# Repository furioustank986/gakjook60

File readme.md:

KiCad libraries get messed up when pulling, so just make sure to manage that

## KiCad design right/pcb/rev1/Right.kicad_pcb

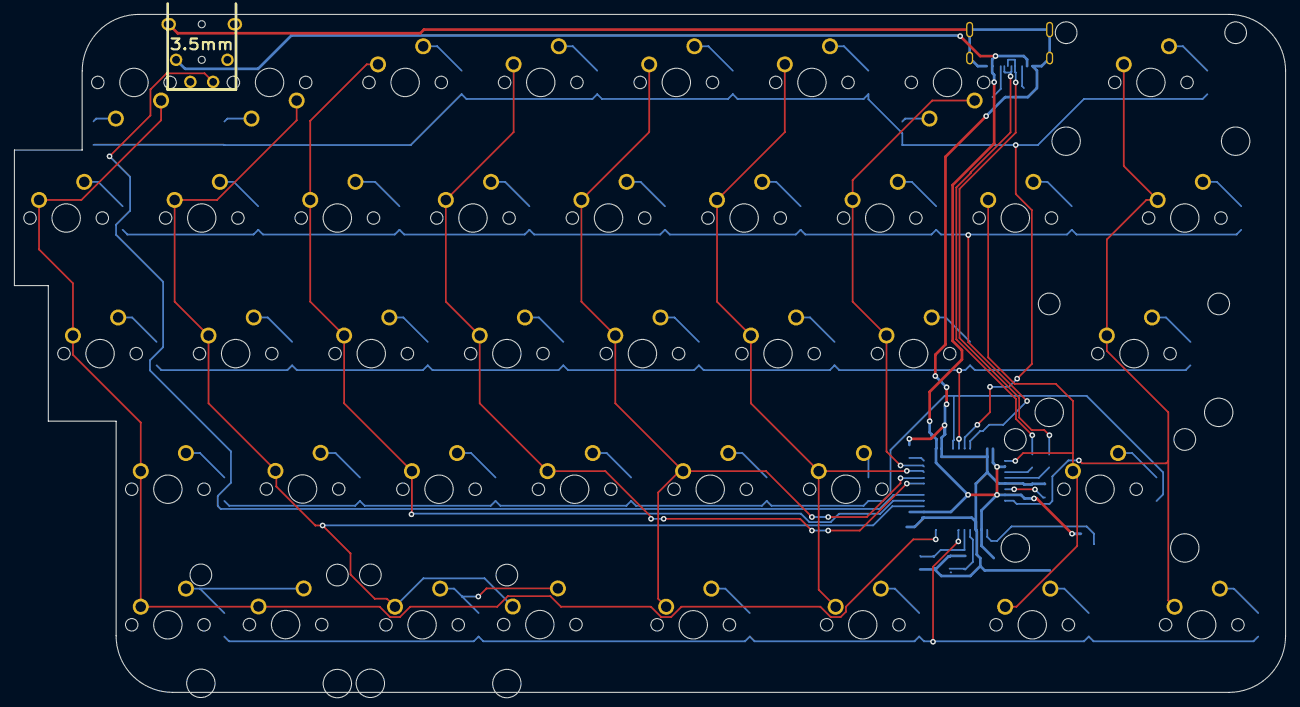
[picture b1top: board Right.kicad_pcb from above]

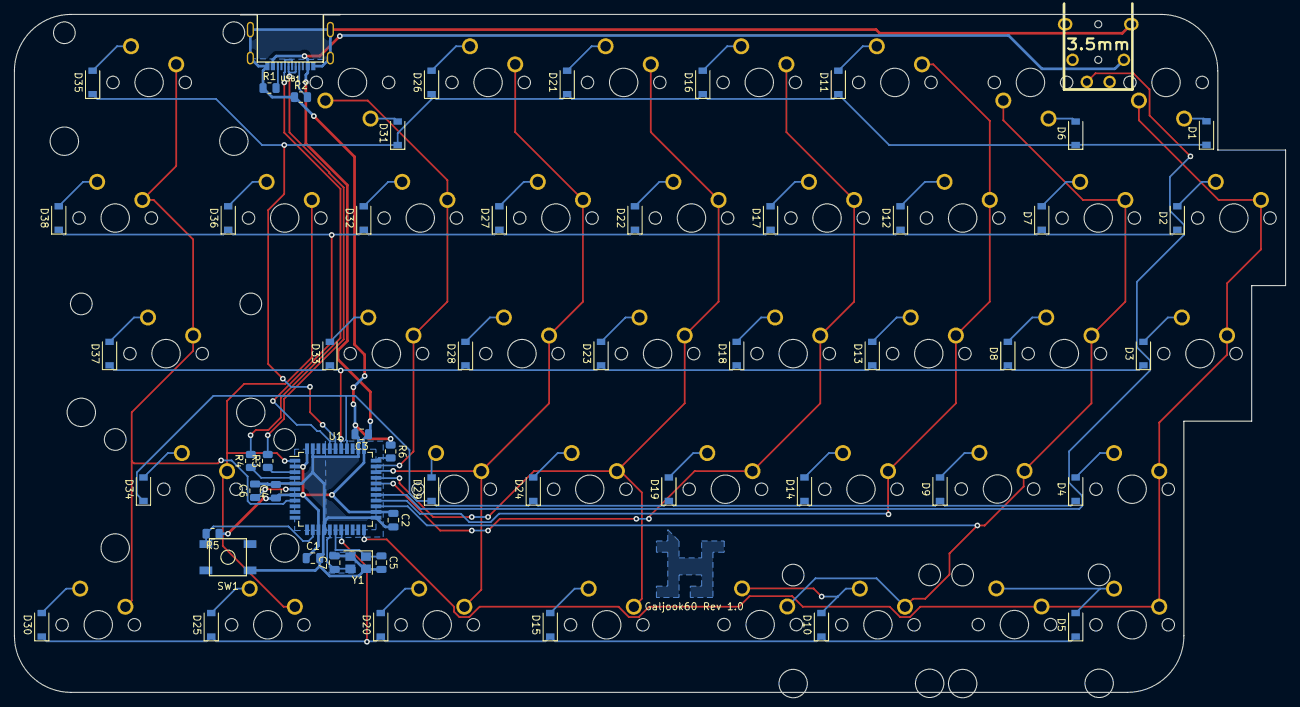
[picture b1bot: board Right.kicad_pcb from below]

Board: 2 copper layers, 178.6 x 95.2 mm, 96 parts (55 on the bottom side), 66 nets.

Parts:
C1, C2, C3: 0.1µF; C_0805_2012Metric
C4: 10µF; C_0805_2012Metric
C5, C7: 22pF; C_0805_2012Metric
C6: 1µF; C_0805_2012Metric
D1, D2, D3, D4, D5, D6, D7, D8, D9, D10, D11, D12, D13, D14, D15, D16, D17, D18, D19, D20, D21, D22, D23, D24, D25, D26, D27, D28, D29, D30, D31, D32, D33, D34, D35, D36, D37, D38: D_Small; D_SOD-123
MX1, MX2, MX3, MX4, MX5, MX6, MX7, MX8, MX9, MX11, MX12, MX13, MX14, MX16, MX17, MX18, MX19, MX21, MX22, MX23, MX24, MX26, MX27, MX28, MX29, MX31, MX32, MX33, MX36, MX40: MX-NoLED; MXOnly-1U-NoLED
MX10, MX34, MX39: MX-NoLED; MXOnly-2.75U-NoLED
MX15, MX20, MX25, MX30: MX-NoLED; MXOnly-1.25U-NoLED
MX35: MX-NoLED; MXOnly-2U-NoLED
MX37: MX-NoLED; MXOnly-2.25U-NoLED
MX38: MX-NoLED; MXOnly-1.5U-NoLED
R1, R2: 5k; R_0805_2012Metric
R3, R4: 22; R_0805_2012Metric
R5, R6: 10k; R_0805_2012Metric
SW1: SW_Push; SKQG-1155865
U1: ATmega32U4-AU; TQFP-44_10x10mm_P0.8mm
U2: TRRS; TRRS_Jack
USB1: HRO-TYPE-C-31-M-12; USB-C-12-Pin-MidMount
Y1: 16MHz; Crystal_SMD_3225-4Pin_3.2x2.5mm

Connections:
+5V: C1.1, C2.1, C3.1, C4.1, R5.1, U1.2, U1.7, U1.14, U1.24, U1.34, U1.44, U2.2, USB1.2, USB1.11
D+: R4.2, USB1.6, USB1.8
D-: R3.2, USB1.5, USB1.7
GND: C1.2, C2.2, C3.2, C4.2, C5.2, C6.2, C7.2, R1.1, R2.1, R6.1, SW1.1, U1.5, U1.15, U1.23, U1.35, U1.43, U2.4, USB1.1, USB1.12, USB1.13, Y1.2, Y1.4
unnamed: C5.1, U1.17, Y1.1
unnamed: C6.1, U1.6
unnamed: C7.1, U1.16, Y1.3
unnamed: D1.2, MX1.2
unnamed: D2.2, MX2.2
unnamed: D3.2, MX3.2
unnamed: D4.2, MX4.2
unnamed: D5.2, MX5.2, MX39.2
unnamed: D6.2, MX6.2
unnamed: D7.2, MX7.2
unnamed: D8.2, MX8.2
unnamed: D9.2, MX9.2
unnamed: D10.2, MX10.2, MX40.2
unnamed: D11.2, MX11.2
unnamed: D12.2, MX12.2
unnamed: D13.2, MX13.2
unnamed: D14.2, MX14.2
unnamed: D15.2, MX15.2
unnamed: D16.2, MX16.2
unnamed: D17.2, MX17.2
unnamed: D18.2, MX18.2
unnamed: D19.2, MX19.2
unnamed: D20.2, MX20.2
unnamed: D21.2, MX21.2
unnamed: D22.2, MX22.2
unnamed: D23.2, MX23.2
unnamed: D24.2, MX24.2
unnamed: D25.2, MX25.2
unnamed: D26.2, MX26.2
unnamed: D27.2, MX27.2
unnamed: D28.2, MX28.2
unnamed: D29.2, MX29.2
unnamed: D30.2, MX30.2
unnamed: D31.2, MX31.2
unnamed: D32.2, MX32.2
unnamed: D33.2, MX33.2
unnamed: D34.2, MX34.2
unnamed: D35.2, MX35.2
unnamed: D36.2, MX36.2
unnamed: D37.2, MX37.2
unnamed: D38.2, MX38.2
unnamed: R1.2, USB1.10
unnamed: R2.2, USB1.4
unnamed: R3.1, U1.3
unnamed: R4.1, U1.4
unnamed: R5.2, SW1.2, U1.13
unnamed: R6.2, U1.33
Split1: U1.27, U2.3
col0: MX1.1, MX2.1, MX3.1, MX4.1, MX5.1, MX39.1, U1.22
col1: MX6.1, MX7.1, MX8.1, MX9.1, MX10.1, MX40.1, U1.25
col2: MX11.1, MX12.1, MX13.1, MX14.1, U1.26
col3: MX16.1, MX17.1, MX18.1, MX19.1, U1.29
col4: MX15.1, MX21.1, MX22.1, MX23.1, MX24.1, U1.30
col5: MX20.1, MX26.1, MX27.1, MX28.1, MX29.1, U1.31
col6: MX31.1, MX32.1, MX33.1, U1.32
col7: MX30.1, MX35.1, MX37.1, MX38.1, U1.8
col8: MX25.1, MX34.1, MX36.1, U1.1
row0: D1.1, D6.1, D11.1, D16.1, D21.1, D26.1, D31.1, D35.1, U1.39
row1: D2.1, D7.1, D12.1, D17.1, D22.1, D27.1, D32.1, D36.1, D38.1, U1.40
row2: D3.1, D8.1, D13.1, D18.1, D23.1, D28.1, D33.1, D37.1, U1.38
row3: D4.1, D9.1, D14.1, D19.1, D24.1, D29.1, D34.1, U1.37
row4: D5.1, D10.1, D15.1, D20.1, D25.1, D30.1, U1.18

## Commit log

2021-04-17 Added keyboard layouts
2021-04-17 Changed layout
2021-04-17 Removed submodule
2021-04-17 Added PCB schematics for the left side
2021-04-18 Routed most of the pcb for the left half
2021-04-18 Finalized PCB for the left side
2021-04-18 added empty right side pcb files
2021-04-18 Added schematic for the PCB for the right side
2021-04-18 added full PCB for the right side
2021-04-18 Properly routed PCB
2021-04-24 updated left side PCB to reflect other split keyboards
2021-05-09 Added proper edge cuts for left side PCB
2021-05-09 Added corrected layout.json for left side
2021-05-11 Added more layouts to bottom spacebar
2021-05-11 added more layouts for right spacebar
2021-05-11 Fixed DRC issues
2021-05-11 fixed logo
2021-05-11 added plate files
